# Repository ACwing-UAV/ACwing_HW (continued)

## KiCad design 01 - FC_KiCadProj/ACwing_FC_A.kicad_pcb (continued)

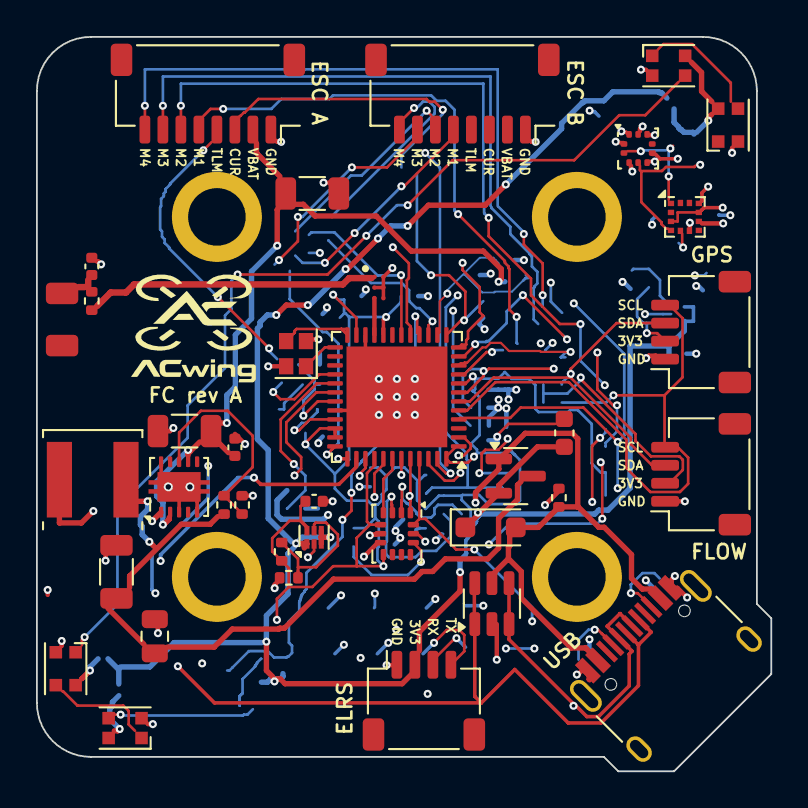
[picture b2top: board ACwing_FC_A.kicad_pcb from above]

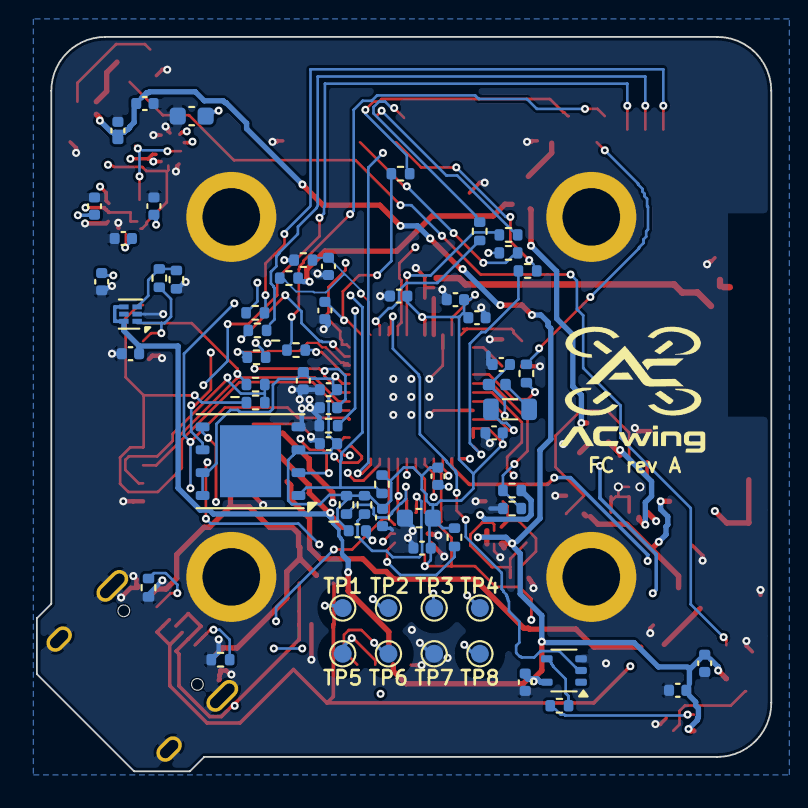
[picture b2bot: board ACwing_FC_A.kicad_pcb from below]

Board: 4 copper layers, 40.8 x 40.8 mm, 109 parts (67 on the bottom side), 68 nets.

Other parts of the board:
LOGO1: ACwing_Logo_Full_6mm
LOGO2: ACwing_Logo_Full_7mm

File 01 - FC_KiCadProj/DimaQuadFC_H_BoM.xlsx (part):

DimaQuadFC rev H - assembly BoM (1 board)
Source: DimaQuadFC_H.kicad_sch / DimaQuadFC_H.kicad_pcb. MPNs = parts as assemb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
Item | Quantity | Part Reference | Value | MPN | Manufacturer | LCSC / JLCPCB # | Package | Description | Side | Notes
1 | 1 | AE1 | 2450AT18A0100001E | 2450AT18A0100001E | Johanson Technology | C17430588 | 1206 (3.2 x 1.6 x 1.3 mm) | Chip antenna, 2.4 GHz, 0.5 dBi, 50 Ohm | Top | Johanson global P/N of the legacy 2450AT18A100E (same part). Left board edge, i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
2 | 18 | C1, C12, C14, C15, C16, C17, C19, C21, C23, C24, C25, C26, C28, C39, C40, C41, 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 | 100nF | CL05B104KO5NNNC | Samsung Electro-Mechanics | C1525 | 0402 (1005 metric) | Capacitor, MLCC, 100 nF, 16 V, X7R, 10% | Bottom | Decoupling (MCU, sensors, NRST). JLC Basic part (replaces Murata GRM155R71C104K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
3 | 2 | C2, C47 | 4.7uF 50V | 1206B475K500NT | FH (Guangdong Fenghua) | C29823 | 1206 (3216 metric), h 1.6 mm | Capacitor, MLCC, 4.7 uF, 50 V, X7R, 10% | Top | VBAT (up to 6S): buck input (C47), ESC link A (C2). JLC Basic part
4 | 1 | C6 | 100uF 6.3V | CL31A107MQHNNNE | Samsung Electro-Mechanics | C15008 | 1206 (3216 metric), h 1.6 mm | Capacitor, MLCC, 100 uF, 6.3 V, X5R, 20% | Top | Buck output (VREG). Replaces Murata GRM31CR60J107ME39L
5 | 1 | C7 | 4.7uF | CL10A475KO8NNNC | Samsung Electro-Mechanics | C19666 | 0603 (1608 metric), h 0.8 mm | Capacitor, MLCC, 4.7 uF, 16 V, X5R, 10% | Top | VSYS (C7) and MCU VDD bulk (C9). JLC Basic part, 16 V rating (replaces Murata G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
6 | 1 | C8 | 1uF | CL05A105KA5NQNC | Samsung Electro-Mechanics | C52923 | 0402 (1005 metric) | Capacitor, MLCC, 1 uF, 25 V, X5R, 10% | Top | LDO output (C8), VDDA (C22). JLC Basic part (replaces Murata GRM155R61A105KE15D)
7 | 1 | C9 | 4.7uF | CL10A475KO8NNNC | Samsung Electro-Mechanics | C19666 | 0603 (1608 metric), h 0.8 mm | Capacitor, MLCC, 4.7 uF, 16 V, X5R, 10% | Bottom | VSYS (C7) and MCU VDD bulk (C9). JLC Basic part, 16 V rating (replaces Murata G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
8 | 1 | C18 | 220nF | CL05B224KO5NNNC | Samsung Electro-Mechanics | C16772 | 0402 (1005 metric) | Capacitor, MLCC, 220 nF, 16 V, X7R, 10% | Bottom | IIS2MDC C1 (ESR < 200 mOhm). Replaces Murata GRM155R71C224KA12D
9 | 1 | C20 | 10uF 6.3V | CL10A106KP8NNNC | Samsung Electro-Mechanics | C19702 | 0603 (1608 metric), h 0.8 mm | Capacitor, MLCC, 10 uF, 10 V, X5R, 10% | Bottom | VDD bulk, bottom side. JLC Basic part, 10 V rating (replaces Murata GRM188R60J1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
10 | 2 | C22, C43 | 1uF | CL05A105KA5NQNC | Samsung Electro-Mechanics | C52923 | 0402 (1005 metric) | Capacitor, MLCC, 1 uF, 25 V, X5R, 10% | Bottom | LDO output (C8), VDDA (C22). JLC Basic part (replaces Murata GRM155R61A105KE15D)
11 | 1 | C27 | 100pF | 0402CG101J500NT | FH (Guangdong Fenghua) | C1546 | 0402 (1005 metric) | Capacitor, MLCC, 100 pF, 50 V, C0G, 5% | Bottom | VDDRF high-frequency decoupling. JLC Basic part (replaces Murata GRM1555C1H101J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
12 | 1 | C29 | 4.7uF | CL05A475MP5NRNC | Samsung Electro-Mechanics | C23733 | 0402 (1005 metric) | Capacitor, MLCC, 4.7 uF, 10 V, X5R, 20% | Bottom | SMPS output (VFBSMPS). Replaces Murata GRM155R61A475MEAAD
13 | 1 | C44 | 2.2uF | CL05A225MQ5NSNC | Samsung Electro-Mechanics | C12530 | 0402 (1005 metric) | Capacitor, MLCC, 2.2 uF, 6.3 V, X5R, 20% | Bottom | Expansion LDO output (VEXP). JLC Basic part
14 | 1 | C46 | 22uF 25V | CL21A226MAQNNNE | Samsung Electro-Mechanics | C45783 | 0805 (2012 metric), h 1.25 mm | Capacitor, MLCC, 22 uF, 25 V, X5R, 20% | Top | Buck output (with C6). JLC Basic part
15 | 1 | C49 | 10nF | CL05B103KB5NNNC | Samsung Electro-Mechanics | C15195 | 0402 (1005 metric) | Capacitor, MLCC, 10 nF, 50 V, X7R, 10% | Top | -. JLC Basic part
16 | 4 | D1, D2, D3, D4 | WS2812B-2020 | WS2812B-2020 | Worldsemi | C965555 | 2.0 x 2.0 x 0.84 mm, 4 pad | LED, RGB addressable, integrated driver, 2.0 x 2.0 mm | Top | Status LEDs: D1 front, D2 rear, one chain from PB6 (TIM16_CH1N + DMA)
17 | 1 | D9 | PMEG2010AEH | PMEG2010AEH,115 | Nexperia | C110921 | SOD-123F | Diode, Schottky, 20 V, 1 A, Vf ~0.35 V | Top | USB VBUS -> VSYS
18 | 1 | D11 | RB521S30 | RB521S30T1G | onsemi | C8523 | SOD-523 | Diode, Schottky, 30 V, 200 mA, SOD-523 | Bottom | VSYS -> VLED (keeps the LEDs below their VDD max with USB 5 V)
19 | 1 | J1 | USB-C (HRO TYPE-C-31-M-12) | TYPE-C-31-M-12 | HRO (Korea Hroparts) | C165948 | USB-C receptacle, 16 pin, SMD + THT shell | Connector, USB Type-C receptacle, USB 2.0, top mount | Top | Mouth 0.35 mm past the right-corner chamfer
20 | 1 | J2 | ESC link | SM08B-SRSS-TB(LF)(SN) | JST | C160407 | JST SH 8P side entry, h 2.9 mm | Connector, JST SH, 8 positions, 1.0 mm pitch, side entry | Top | ESC links (top side): J2 ESC A rear edge (power, CUR, M1-M4); J6 ESC B left edg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
21 | 2 | J3, J4 | Qwiic | SM04B-SRSS-TB(LF)(SN) | JST | C160404 | JST SH 4P side entry, SMD, h 2.9 mm | Connector, JST SH, 4 positions, 1.0 mm pitch, side entry, SMD | Top | Qwiic / STEMMA QT expansion port (GPS, flow): 1 GND, 2 3.3 V, 3 SDA, 4 SCL. Qwi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
22 | 1 | J5 | ELRS | SM04B-SRSS-TB(LF)(SN) | JST | C160404 | JST SH 4P side entry, SMD, h 2.9 mm | Connector, JST SH, 4 positions, 1.0 mm pitch, side entry, SMD | Top | ELRS receiver port (CRSF, USART1): 1 GND, 2 VSYS, 3 RX, 4 TX. ELRS receiver por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
23 | 1 | J6 | ESC link B | SM08B-SRSS-TB(LF)(SN) | JST | C160407 | JST SH 8P side entry, h 2.9 mm | Connector, JST SH, 8 positions, 1.0 mm pitch, side entry | Top | ESC link B (M5-M8), top side, left edge, mouth toward the left
24 | 1 | L1 | 2.2uH | MPH201210S2R2MT | Sunlord | C55755 | 0805 (2012 metric), h 1.0 mm | Inductor, multilayer power, 2.2 uH, 20%, 420 mA, DCR 0.25 Ohm, 2.0 x 1.2 x 1.0 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 | Bottom | SMPS inductor for the 8 MHz SMPS clock (DS13252 table 6). SMPS inductor, 8 MHz 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
25 | 1 | L2 | 10nH | LQG15HS10NJ02D | Murata | C77103 | 0402 (1005 metric) | Inductor, multilayer, 10 nH, 5%, 500 mA | Bottom | SMPS output filter, AN5290. Replaces LQG15WZ10NJ02D (same value, LCSC stocked)
26 | 1 | L3 | 22uH | SWPA5040S220MT | Sunlord | C68434 | SMD 5 x 5 x 4 mm, shielded | Inductor, shielded power, 22 uH, 20%, Irated 1.5 A, Isat 1.9 A, DCR 168 mOhm, 5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 | Top | Input buck inductor (top, rear-left corner)
27 | 1 | Q5 | AO3401A | AO3401A | Alpha & Omega Semiconductor | C15127 | SOT-23 | MOSFET, P-channel, 30 V, 4 A | Top | Battery/USB load sharing
28 | 1 | R2 | 100k | 0402WGF1003TCE | UNI-ROYAL | C25741 | 0402 (1005 metric) | Resistor, 100 kOhm, 1%, 1/16 W | Top | Q5 gate pull-down (R2), VBUS sense divider (R10, R11). JLC Basic part
29 | 1 | R3 | 287k 1% | RC-02K2873FT | FH (Guangdong Fenghua) | C42921050 | 0402 (1005 metric) | Resistor, 287 kOhm, 1%, 1/16 W | Top | LDO feedback (VOUT = 3.10 V)
30 | 1 | R4 | 100k 1% | 0402WGF1003TCE | UNI-ROYAL | C25741 | 0402 (1005 metric) | Resistor, 100 kOhm, 1%, 1/16 W | Top | LDO feedback (R4), VBAT sense divider top (R8). JLC Basic part
31 | 1 | R8 | 100k 1% | 0402WGF1003TCE | UNI-ROYAL | C25741 | 0402 (1005 metric) | Resistor, 100 kOhm, 1%, 1/16 W | Bottom | LDO feedback (R4), VBAT sense divider top (R8). JLC Basic part
32 | 4 | R9, R14, R37, R38 | 10k | 0402WGF1002TCE | UNI-ROYAL | C25744 | 0402 (1005 metric) | Resistor, 10 kOhm, 1%, 1/16 W | Bottom | BOOT0 pull-down (R14), FLASH_CS / IMU_CS pull-ups (R37, R38), VBAT sense divide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
33 | 2 | R10, R11 | 100k | 0402WGF1003TCE | UNI-ROYAL | C25741 | 0402 (1005 metric) | Resistor, 100 kOhm, 1%, 1/16 W | Bottom | Q5 gate pull-down (R2), VBUS sense divider (R10, R11). JLC Basic part
34 | 2 | R12, R13 | 5.1k | 0402WGF5101TCE | UNI-ROYAL | C25905 | 0402 (1005 metric) | Resistor, 5.1 kOhm, 1%, 1/16 W | Bottom | USB-C CC pull-downs. JLC Basic part
35 | 2 | R15, R16 | 2.2k | 0402WGF2201TCE | UNI-ROYAL | C25879 | 0402 (1005 metric) | Resistor, 2.2 kOhm, 1%, 1/16 W | Bottom | I2C1 pull-ups. JLC Basic part
36 | 2 | R17, R18 | 4.7k | 0402WGF4701TCE | UNI-ROYAL | C25900 | 0402 (1005 metric) | Resistor, 4.7 kOhm, 1%, 1/16 W | Bottom | Sensor hub pull-ups. JLC Basic part
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
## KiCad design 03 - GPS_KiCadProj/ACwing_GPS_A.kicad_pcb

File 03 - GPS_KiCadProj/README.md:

# ACwing GPS rev A – KiCad project

**Project:** ACwing · **Author:** Andrea Cirillo

KiCad sources of the ACwing GPS rev A board (KiCad 10 project files, 2026-11-07). The board description, schematic PDF, BoM,
JLCPCB files, Gerber, STEP and board views are in [`00 - Docs/02 - GPS_Docs`](../00%20-%20Docs/02%20-%20GPS_Docs/).

| File / folder | What |
|---|---|
| `ACwing_GPS_A.kicad_pro`, `.kicad_sch`, `.kicad_pcb` | project, schematic, routed PCB |
| `*.kicad_sym`, `*.pretty/`, `fp-lib-table`, `sym-lib-table` | project library (symbols, footprints, ACwing logos) |
| `3d/` | STEP models, referenced as `${KIPRJMOD}/3d/...` |
| `generator/` | scripts that generated, routed and checked the design (build_all_gps.sh) |

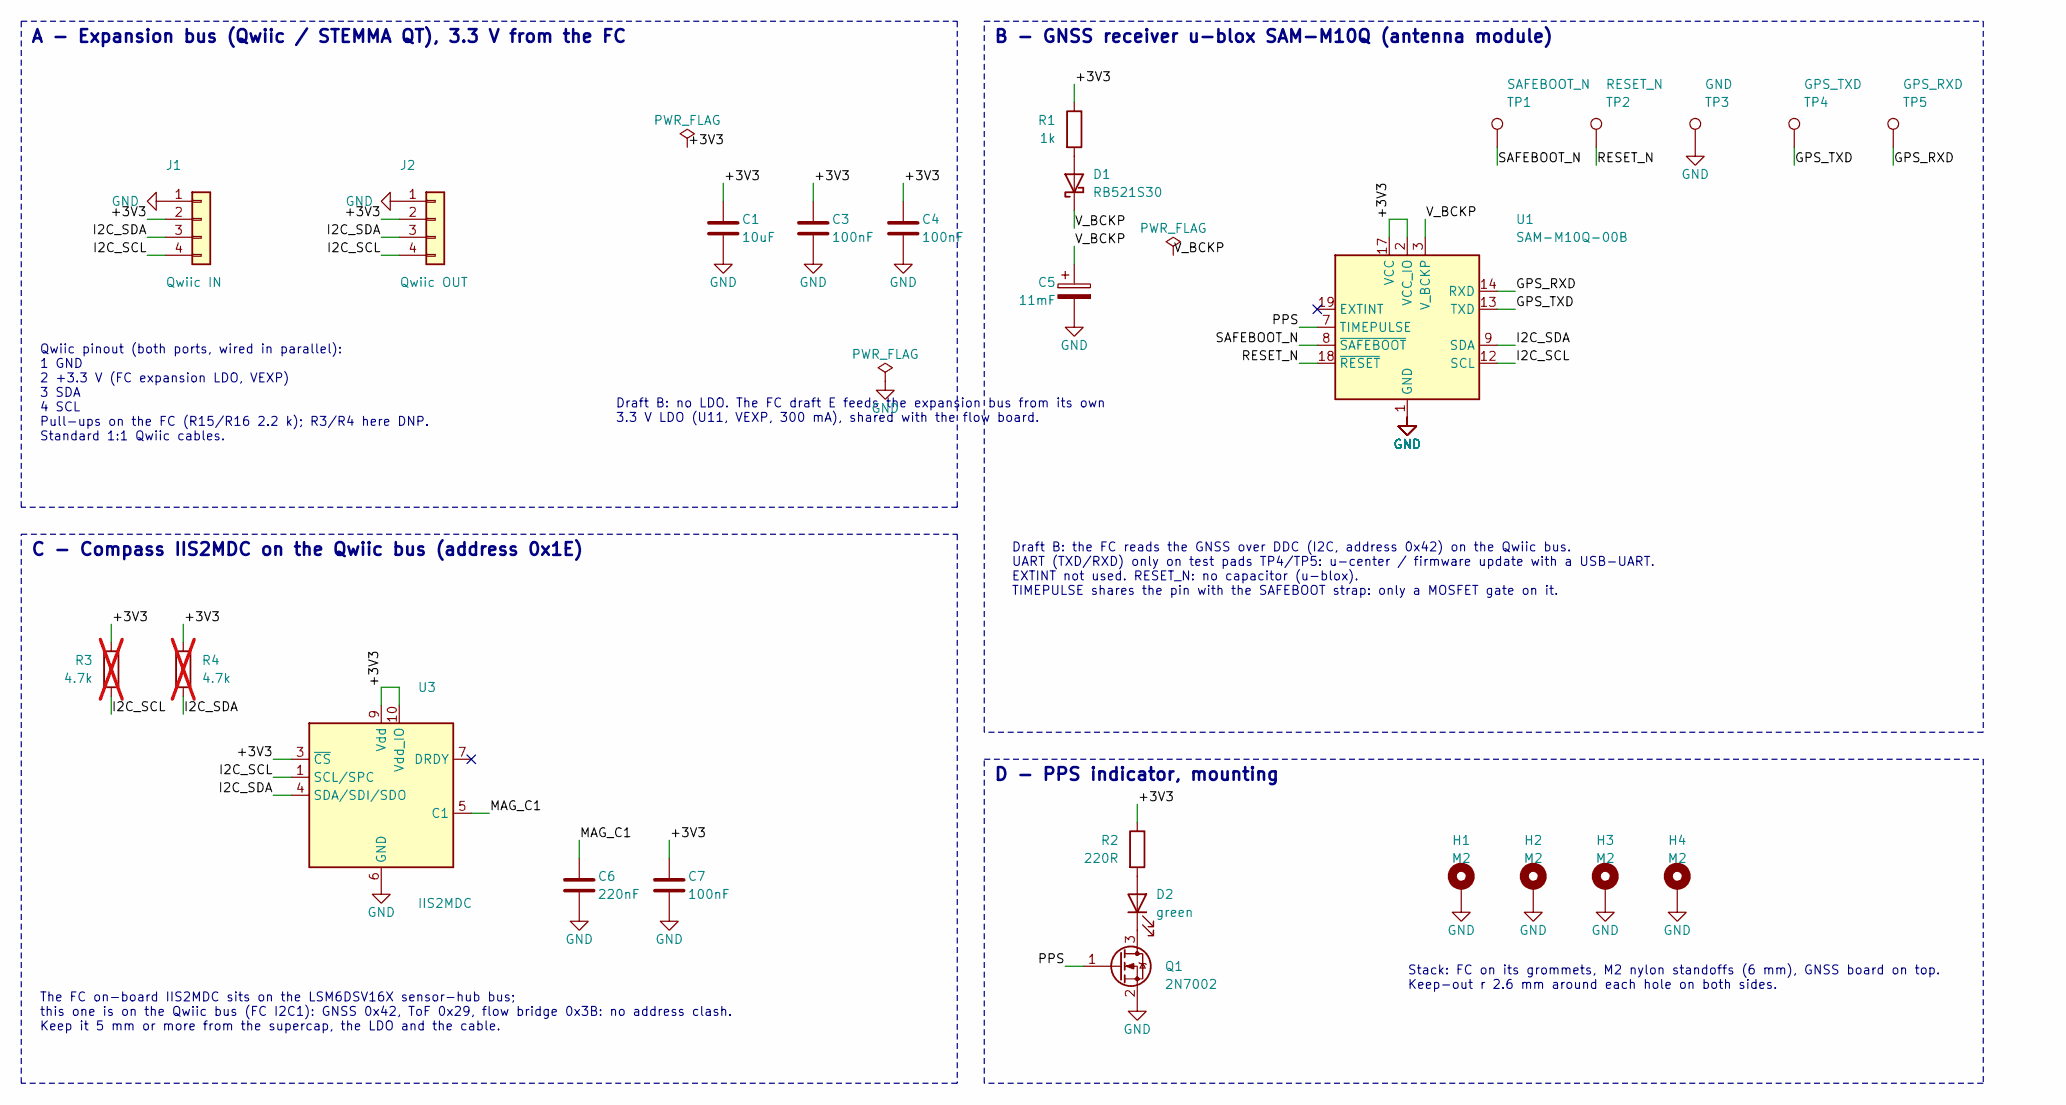
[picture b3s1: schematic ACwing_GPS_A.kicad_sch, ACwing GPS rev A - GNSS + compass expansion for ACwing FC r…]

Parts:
C1: 10uF; C_0603_1608Metric
C3, C4, C7: 100nF; C_0402_1005Metric
C5: 11mF; C_1210_3225Metric
C6: 220nF; C_0402_1005Metric
D1: RB521S30; D_SOD-523
D2: green; LED_0402_1005Metric
H1, H2, H3, H4: M2; MountingHole_PTH_2.2mm_M2_Pad3.6mm
J1: Qwiic IN; JST_SH_SM04B-SRSS-TB_1x04-1MP_P1.00mm_Horizontal
J2: Qwiic OUT; JST_SH_SM04B-SRSS-TB_1x04-1MP_P1.00mm_Horizontal
Q1: 2N7002; SOT-23
R1: 1k; R_0402_1005Metric
R2: 220R; R_0402_1005Metric
R3, R4: 4.7k; R_0402_1005Metric; not fitted
TP1: SAFEBOOT_N; TestPoint_Pad_D1.0mm
TP2: RESET_N; TestPoint_Pad_D1.0mm
TP3: GND; TestPoint_Pad_D1.0mm
TP4: GPS_TXD; TestPoint_Pad_D1.0mm
TP5: GPS_RXD; TestPoint_Pad_D1.0mm
U1: SAM-M10Q-00B; ublox_SAM-M8Q
U3: IIS2MDC; LGA-12_2x2mm_P0.5mm

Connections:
+3V3: C1.1, C3.1, C4.1, C7.1, J1.2, J2.2, R1.1, R2.1, R3.1, R4.1, U1.2 (VCC_IO), U1.17 (VCC), U3.3 (~CS), U3.9 (Vdd), U3.10 (Vdd_IO)
GND: C1.2, C3.2, C4.2, C5.2, C6.2, C7.2, H1.1, H2.1, H3.1, H4.1, J1.1, J2.1, Q1.2 (S), TP3.1, U1.1 (GND), U1.4 (GND), U1.5 (GND), U1.6 (GND), U1.10 (GND), U1.11 (GND), U1.15 (GND), U1.16 (GND), U1.20 (GND), U3.6 (GND), U3.8 (GND)
GPS_RXD: TP5.1, U1.14 (RXD)
GPS_TXD: TP4.1, U1.13 (TXD)
I2C_SCL: J1.4, J2.4, R3.2, U1.12 (SCL), U3.1 (SCL/SPC)
I2C_SDA: J1.3, J2.3, R4.2, U1.9 (SDA), U3.4 (SDA/SDI/SDO)
MAG_C1: C6.1, U3.5 (C1)
unnamed: D1.2 (A), R1.2
unnamed: D2.2 (A), R2.2
unnamed: D2.1 (K), Q1.3 (D)
PPS: Q1.1 (G), U1.7 (TIMEPULSE)
RESET_N: TP2.1, U1.18 (~RESET)
SAFEBOOT_N: TP1.1, U1.8 (~SAFEBOOT)
V_BCKP: C5.1, D1.1 (K), U1.3 (V_BCKP)

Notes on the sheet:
Stack: FC on its grommets, M2 nylon standoffs (6 mm), GNSS board on top. Keep-out r 2.6 mm around each hole on both sides.
Qwiic pinout (both ports, wired in parallel): 1 GND 2 +3.3 V (FC expansion LDO, VEXP) 3 SDA 4 SCL Pull-ups on the FC (R15/R16 2.2 k); R3/R4 here DNP. Standard 1:1 Qwiic cables.
Draft B: no LDO. The FC draft E feeds the expansion bus from its own 3.3 V LDO (U11, VEXP, 300 mA), shared with the flow board.
B - GNSS receiver u-blox SAM-M10Q (antenna module)
Draft B: the FC reads the GNSS over DDC (I2C, address 0x42) on the Qwiic bus. UART (TXD/RXD) only on test pads TP4/TP5: u-center / firmware update with a USB-UART. EXTINT not used. RESET_N: no capacitor (u-blox). TIMEPULSE shares the pin with the SAFEBOOT strap: only a MOSFET gate on it.
A - Expansion bus (Qwiic / STEMMA QT), 3.3 V from the FC
The FC on-board IIS2MDC sits on the LSM6DSV16X sensor-hub bus; this one is on the Qwiic bus (FC I2C1): GNSS 0x42, ToF 0x29, flow bridge 0x3B: no address clash. Keep it 5 mm or more from the supercap, the LDO and the cable.
C - Compass IIS2MDC on the Qwiic bus (address 0x1E)
D - PPS indicator, mounting

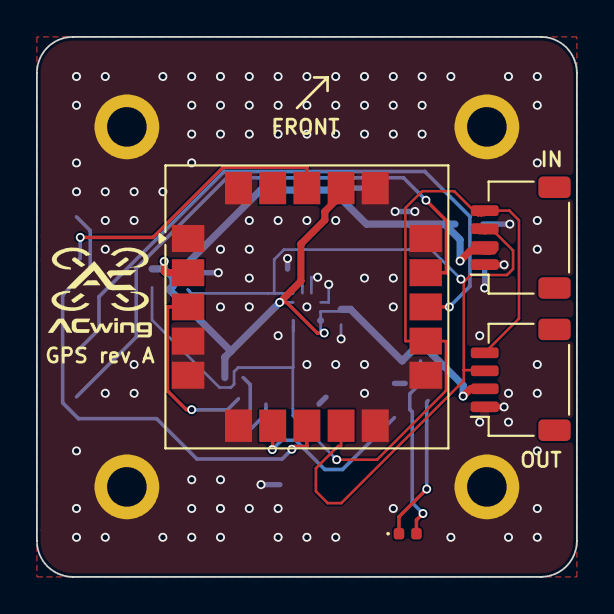
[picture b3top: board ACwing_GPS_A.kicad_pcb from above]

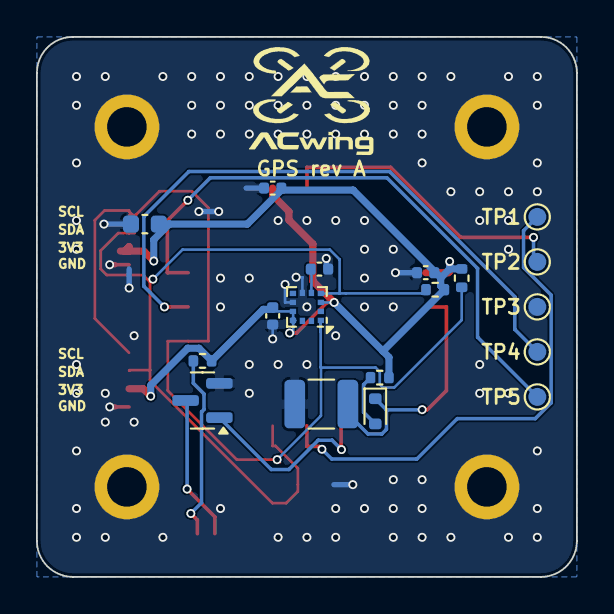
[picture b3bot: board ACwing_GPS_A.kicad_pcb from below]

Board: 2 copper layers, 30.0 x 30.0 mm, 28 parts (19 on the bottom side), 14 nets.

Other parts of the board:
LOGO1: ACwing_Logo_Full_5mm
LOGO2: ACwing_Logo_Full_6mm

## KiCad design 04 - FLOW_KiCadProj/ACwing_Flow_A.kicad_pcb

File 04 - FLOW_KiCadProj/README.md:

# ACwing Flow rev A – KiCad project

**Project:** ACwing · **Author:** Andrea Cirillo

KiCad sources of the ACwing Flow rev A board (KiCad 10 project files, 2026-11-07). The board description, schematic PDF, BoM,
JLCPCB files, Gerber, STEP and board views are in [`00 - Docs/03 - FLOW_Docs`](../00%20-%20Docs/03%20-%20FLOW_Docs/).

| File / folder | What |
|---|---|
| `ACwing_Flow_A.kicad_pro`, `.kicad_sch`, `.kicad_pcb` | project, schematic, routed PCB |
| `*.kicad_sym`, `*.pretty/`, `fp-lib-table`, `sym-lib-table` | project library (symbols, footprints, ACwing logos) |
| `3d/` | STEP models, referenced as `${KIPRJMOD}/3d/...` |
| `generator/` | scripts that generated, routed and checked the design (run_sch.sh, gen_pcb_flow.py, loop_route.sh, post_route.sh) |

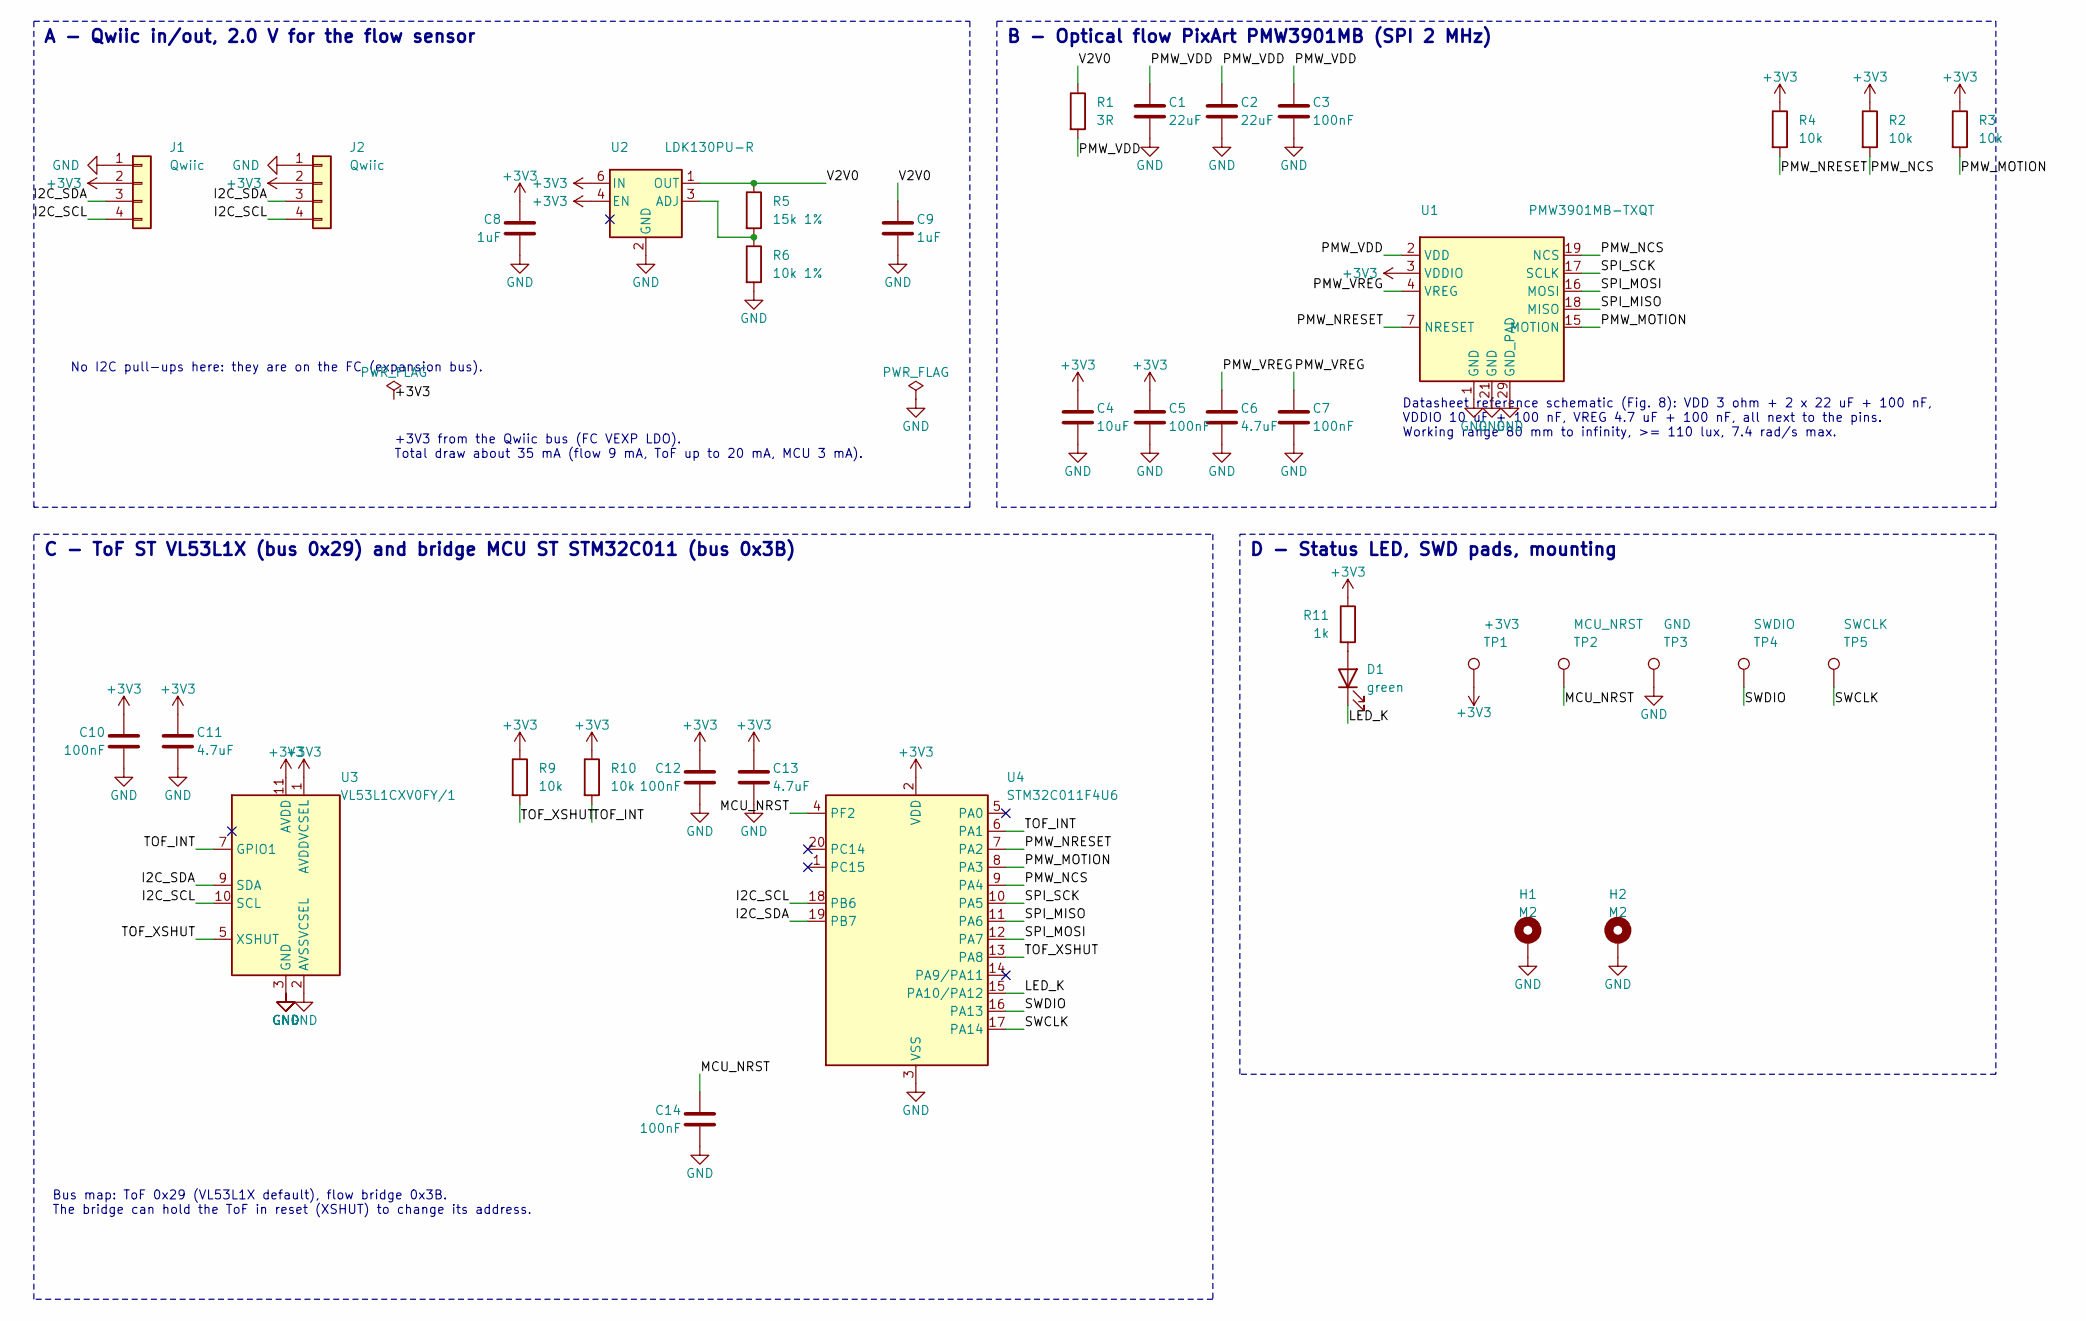
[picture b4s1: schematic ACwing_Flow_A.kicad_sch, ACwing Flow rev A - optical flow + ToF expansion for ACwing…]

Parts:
C1, C2: 22uF; C_0603_1608Metric
C3, C5, C7, C10, C12, C14: 100nF; C_0402_1005Metric
C4: 10uF; C_0603_1608Metric
C6, C11, C13: 4.7uF; C_0603_1608Metric
C8, C9: 1uF; C_0402_1005Metric
D1: green; LED_0402_1005Metric
H1, H2: M2; MountingHole_PTH_2.2mm_M2_Pad3.6mm
J1, J2: Qwiic; JST_SH_SM04B-SRSS-TB_1x04-1MP_P1.00mm_Horizontal
R1: 3R; R_0402_1005Metric
R2, R3, R4, R9, R10: 10k; R_0402_1005Metric
R5: 15k 1%; R_0402_1005Metric
R6: 10k 1%; R_0402_1005Metric
R11: 1k; R_0402_1005Metric
TP1: +3V3; TestPoint_Pad_D1.0mm
TP2: MCU_NRST; TestPoint_Pad_D1.0mm
TP3: GND; TestPoint_Pad_D1.0mm
TP4: SWDIO; TestPoint_Pad_D1.0mm
TP5: SWCLK; TestPoint_Pad_D1.0mm
U1: PMW3901MB-TXQT; PixArt_PMW3901MB_COB-28_6x6mm
U2: LDK130PU-R; DFN-6_1.3x1.2mm_P0.4mm
U3: VL53L1CXV0FY/1; ST_VL53L1x
U4: STM32C011F4U6; ST_UFQFPN-20_3x3mm_P0.5mm

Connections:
+3V3: C4.1, C5.1, C8.1, C10.1, C11.1, C12.1, C13.1, J1.2, J2.2, R2.1, R3.1, R4.1, R9.1, R10.1, R11.1, TP1.1, U1.3 (VDDIO), U2.4 (EN), U2.6 (IN), U3.1 (AVDDVCSEL), U3.11 (AVDD), U4.2 (VDD)
GND: C1.2, C2.2, C3.2, C4.2, C5.2, C6.2, C7.2, C8.2, C9.2, C10.2, C11.2, C12.2, C13.2, C14.2, H1.1, H2.1, J1.1, J2.1, R6.2, TP3.1, U1.1 (GND), U1.21 (GND), U1.29 (GND_PAD), U2.2 (GND), U3.2 (AVSSVCSEL), U3.3 (GND), U3.4 (GND), U3.6 (GND), U3.12 (GND), U4.3 (VSS)
I2C_SCL: J1.4, J2.4, U3.10 (SCL), U4.18 (PB6)
I2C_SDA: J1.3, J2.3, U3.9 (SDA), U4.19 (PB7)
LED_K: D1.1 (K), U4.15 (PA10/PA12)
MCU_NRST: C14.1, TP2.1, U4.4 (PF2)
unnamed: D1.2 (A), R11.2
unnamed: R5.2, R6.1, U2.3 (ADJ)
PMW_MOTION: R3.2, U1.15 (MOTION), U4.8 (PA3)
PMW_NCS: R2.2, U1.19 (NCS), U4.9 (PA4)
PMW_NRESET: R4.2, U1.7 (NRESET), U4.7 (PA2)
PMW_VDD: C1.1, C2.1, C3.1, R1.2, U1.2 (VDD)
PMW_VREG: C6.1, C7.1, U1.4 (VREG)
SPI_MISO: U1.18 (MISO), U4.11 (PA6)
SPI_MOSI: U1.16 (MOSI), U4.12 (PA7)
SPI_SCK: U1.17 (SCLK), U4.10 (PA5)
SWCLK: TP5.1, U4.17 (PA14)
SWDIO: TP4.1, U4.16 (PA13)
TOF_INT: R10.2, U3.7 (GPIO1), U4.6 (PA1)
TOF_XSHUT: R9.2, U3.5 (XSHUT), U4.13 (PA8)
V2V0: C9.1, R1.1, R5.1, U2.1 (OUT)

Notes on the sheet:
Bus map: ToF 0x29 (VL53L1X default), flow bridge 0x3B. The bridge can hold the ToF in reset (XSHUT) to change its address.
C - ToF ST VL53L1X (bus 0x29) and bridge MCU ST STM32C011 (bus 0x3B)
No I2C pull-ups here: they are on the FC (expansion bus).
+3V3 from the Qwiic bus (FC VEXP LDO). Total draw about 35 mA (flow 9 mA, ToF up to 20 mA, MCU 3 mA).
B - Optical flow PixArt PMW3901MB (SPI 2 MHz)
Datasheet reference schematic (Fig. 8): VDD 3 ohm + 2 x 22 uF + 100 nF, VDDIO 10 uF + 100 nF, VREG 4.7 uF + 100 nF, all next to the pins. Working range 80 mm to infinity, >= 110 lux, 7.4 rad/s max.
D - Status LED, SWD pads, mounting
A - Qwiic in/out, 2.0 V for the flow sensor

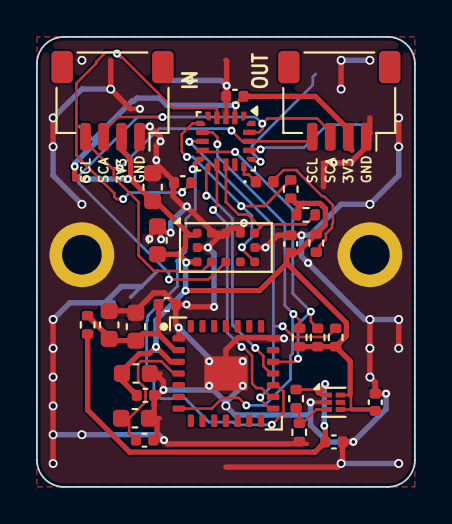
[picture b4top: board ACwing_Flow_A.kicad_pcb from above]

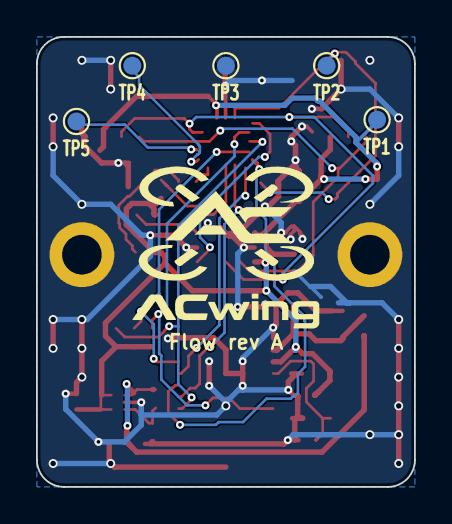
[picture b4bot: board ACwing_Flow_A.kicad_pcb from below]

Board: 2 copper layers, 21.0 x 25.0 mm, 38 parts (6 on the bottom side), 21 nets.

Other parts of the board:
LOGO1: ACwing_Logo_Full_9mm

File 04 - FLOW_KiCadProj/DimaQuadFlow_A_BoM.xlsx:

DimaQuadFlow rev A - assembly BoM (1 board)
Source: DimaQuadFlow_A.kicad_sch / DimaQuadFlow_A.kicad_pcb. LCSC part numbers 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
Item | Quantity | Part Reference | Value | MPN | Manufacturer | LCSC / JLCPCB # | Package | Description | Side | Notes
1 | 2 | C1, C2 | 22uF | CL10A226MQ8NRNC | Samsung Electro-Mechanics | C59461 | 0603 (1608 metric) | Capacitor, MLCC, 22 uF, 6.3 V, X5R | Top | PMW3901 VDD (PixArt reference)
2 | 6 | C3, C5, C7, C10, C12, C14 | 100nF | CL05B104KO5NNNC | Samsung Electro-Mechanics | C1525 | 0402 (1005 metric) | Capacitor, MLCC, 100 nF, 16 V, X7R | Top | Decoupling
3 | 1 | C4 | 10uF | CL10A106KP8NNNC | Samsung Electro-Mechanics | C19702 | 0603 (1608 metric) | Capacitor, MLCC, 10 uF, 10 V, X5R | Top | PMW3901 VDDIO
4 | 3 | C6, C11, C13 | 4.7uF | CL10A475KO8NNNC | Samsung Electro-Mechanics | C19666 | 0603 (1608 metric) | Capacitor, MLCC, 4.7 uF, 16 V, X5R | Top | PMW3901 VREG, VL53L1X and MCU bulk
5 | 2 | C8, C9 | 1uF | CL05A105KA5NQNC | Samsung Electro-Mechanics | C52923 | 0402 (1005 metric) | Capacitor, MLCC, 1 uF, 25 V, X5R | Top | LDO input / output
6 | 1 | D1 | green | XL-1005UGC | XINGLIGHT | C965793 | 0402 (1005 metric) | LED, green, 0402 | Top | Status LED (PA8)
7 | 2 | J1, J2 | Qwiic | SM04B-SRSS-TB(LF)(SN) | JST | C160404 | JST SH 4P side entry, h 2.9 mm | Connector, JST SH, 4 positions, 1.0 mm pitch, side entry | Top | Qwiic in/out (pass-through), left and right edges
8 | 1 | R1 | 3R | 0402WGF300KTCE | UNI-ROYAL | C423196 | 0402 (1005 metric) | Resistor, 3 Ohm, 1 %, 1/16 W | Top | PMW3901 VDD filter (PixArt reference)
9 | 5 | R2, R3, R4, R9, R10 | 10k | 0402WGF1002TCE | UNI-ROYAL | C25744 | 0402 (1005 metric) | Resistor, 10 kOhm, 1 %, 1/16 W | Top | Pull-ups (NRESET, NCS, MOTION, XSHUT, INT)
10 | 1 | R5 | 15k 1% | 0402WGF1502TCE | UNI-ROYAL | C25756 | 0402 (1005 metric) | Resistor, 15 kOhm, 1 %, 1/16 W | Top | LDO divider, top
11 | 1 | R6 | 10k 1% | 0402WGF1002TCE | UNI-ROYAL | C25744 | 0402 (1005 metric) | Resistor, 10 kOhm, 1 %, 1/16 W | Top | LDO divider, bottom
12 | 1 | R11 | 1k | 0402WGF1001TCE | UNI-ROYAL | C11702 | 0402 (1005 metric) | Resistor, 1 kOhm, 1 %, 1/16 W | Top | LED current
13 | 1 | U1 | PMW3901MB-TXQT | PMW3901MB-TXQT | PixArt Imaging | C43496881 | COB-28 6 x 6 mm (lens 6 x 6 x 2.28) | Optical flow sensor, far field (80 mm to infinity), SPI 2 MHz | Top | Needs the LN03-ZSZ lens assembly: check whether the LCSC/JLC part includes it, 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
14 | 1 | U2 | LDK130PU-R | LDK130PU-R | STMicroelectronics | C157446 | DFN-6 1.2 x 1.3 mm | LDO, adjustable, 300 mA | Top | PMW3901 VDD 2.0 V (R5/R6)
15 | 1 | U3 | VL53L1CXV0FY/1 | VL53L1CXV0FY/1 | STMicroelectronics | C190004 | LGA-12 4.9 x 2.5 x 1.56 mm | Time-of-flight distance sensor, up to 4 m, I2C 0x29 | Top | Height above ground; keep the cover-glass area clear (no window)
16 | 1 | U4 | STM32C011F4U6 | STM32C011F4U6TR | STMicroelectronics | C5456188 | UFQFPN-20 3 x 3 mm | MCU Cortex-M0+, 48 MHz, 16 KB flash, 6 KB RAM | Top | Flow bridge: reads the PMW3901 on SPI, I2C target 0x3B on the Qwiic bus
Total | 30 | Total placements (assembled parts) | - | 16 | line items | - | - | - | - | Not-assembled items listed below
Not assembled (PCB features / DNP)
Item | Quantity | Part Reference | Value | MPN | Manufacturer | LCSC / JLCPCB # | Package | Description | Side | Notes
NA1 | 2 | H1, H2 | M2 | N/A (PCB feature) | N/A | N/A | NPTH 2.2 mm | Mounting hole, M2, 16 x 16 pattern | Top | Keep-out r 2.4 mm on both sides for the nylon screw / standoff
NA2 | 5 | TP1, TP2, TP3, TP4, TP5 | Test pad | N/A (PCB feature) | N/A | N/A | SMD pad 1.0 mm | SWD pads: SWDIO, SWCLK, NRST, 3.3 V, GND | Top | First programming of the STM32C011 with a pogo fixture or tag-connect style pro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
